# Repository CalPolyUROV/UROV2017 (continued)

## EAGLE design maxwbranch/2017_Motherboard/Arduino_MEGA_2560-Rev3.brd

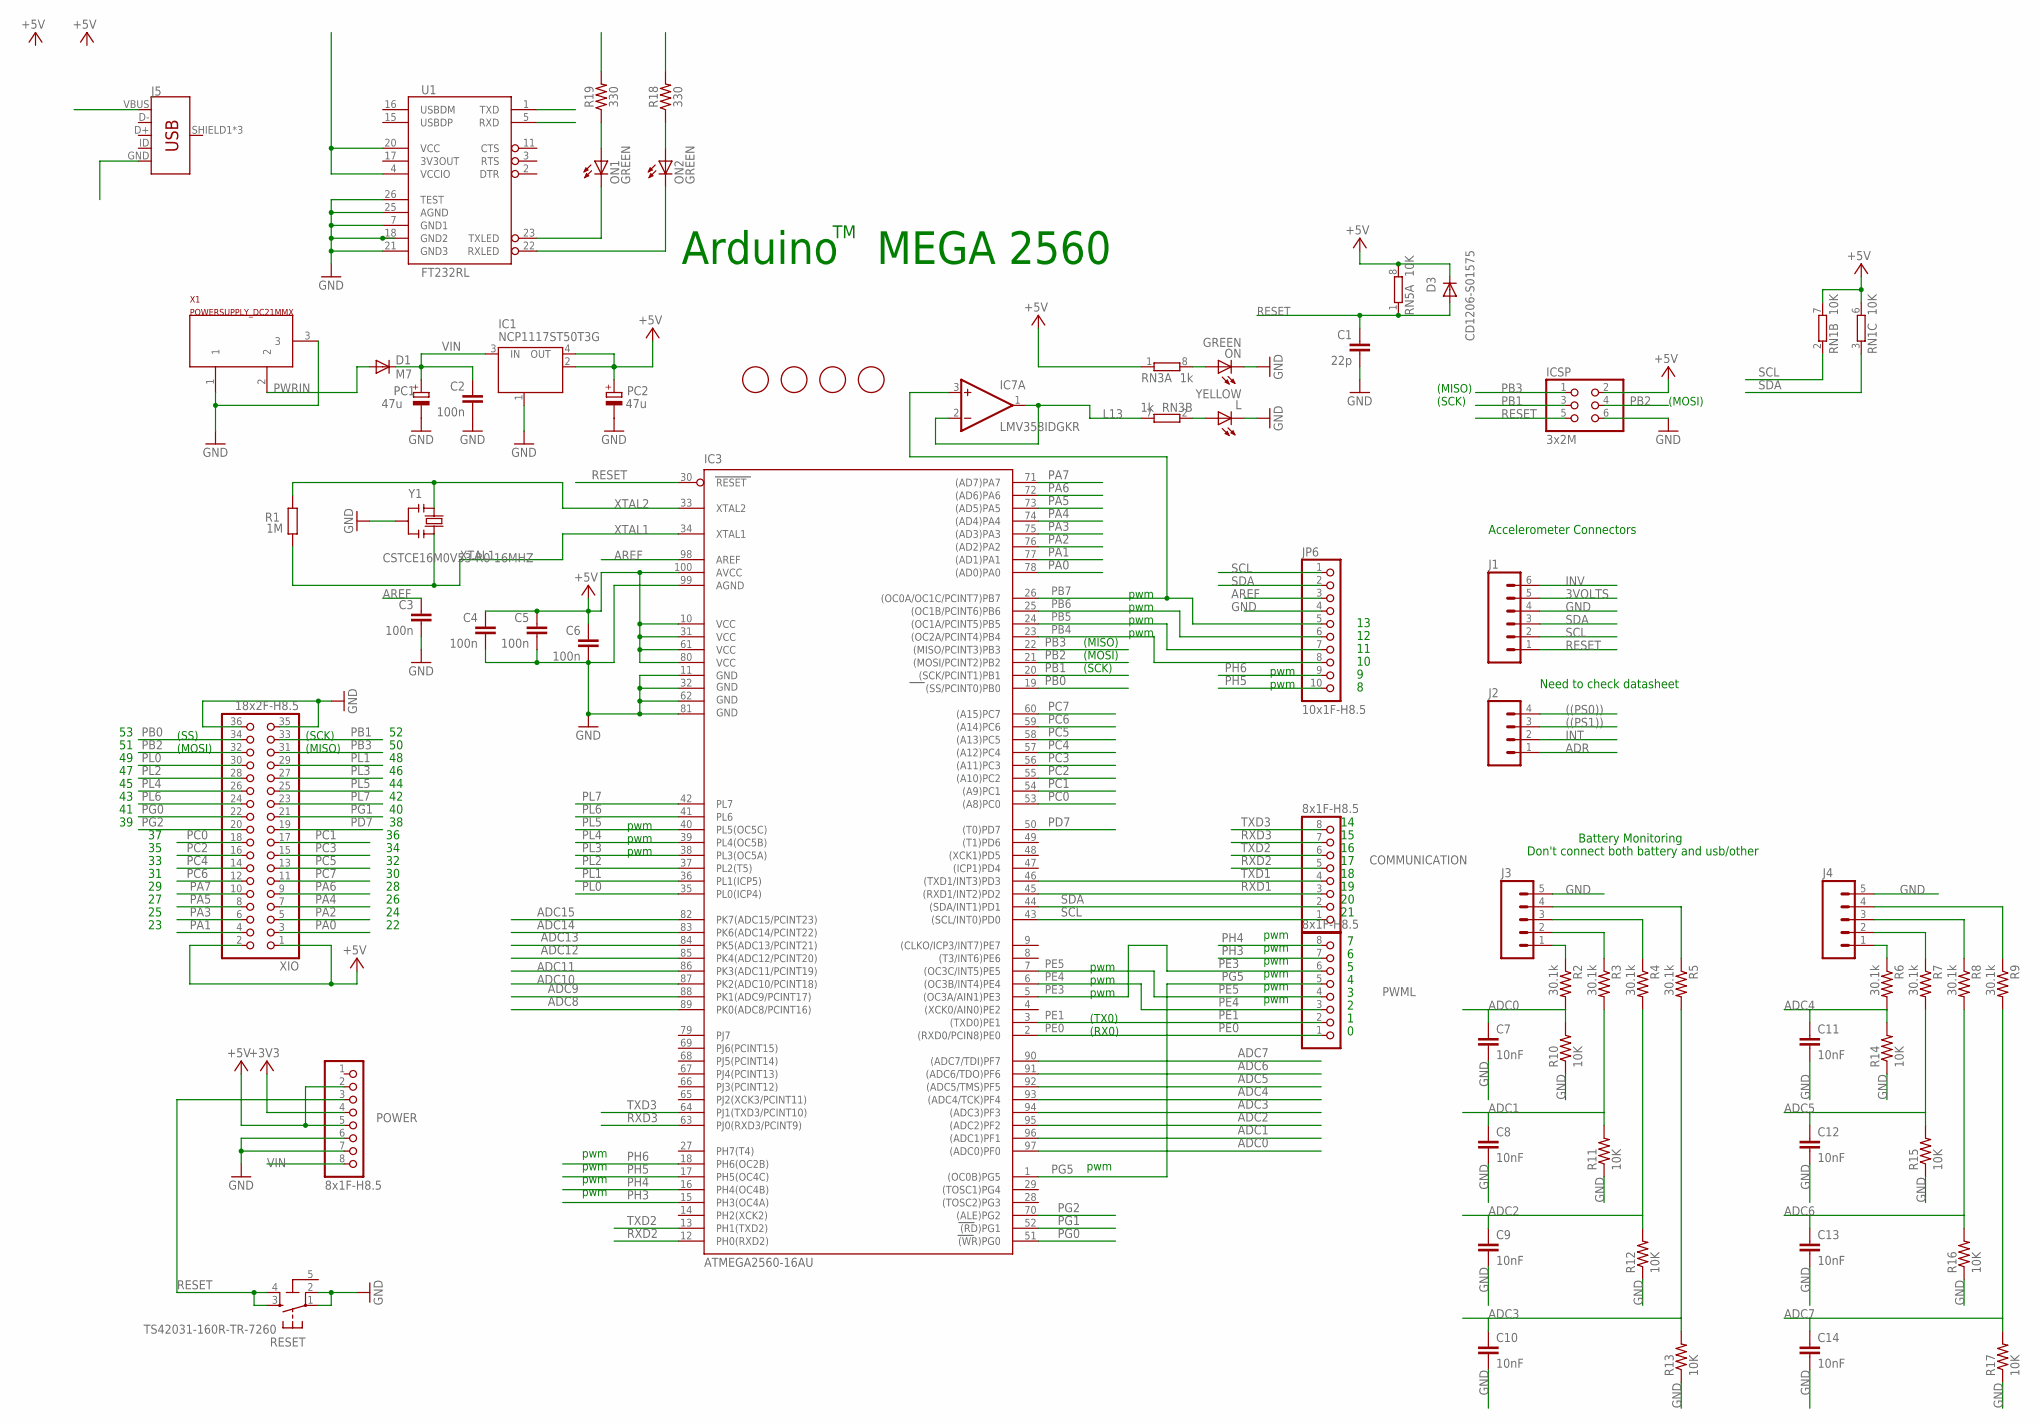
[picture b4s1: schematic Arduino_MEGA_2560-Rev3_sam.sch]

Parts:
C1: 22p; C0603-ROUND
C2, C3, C4, C5, C6: 100n; C0603-ROUND
C7, C8, C9, C10, C11, C12, C13, C14: 10nF; 0603-CAP
COMMUNICATION: 8x1F-H8.5; 1X08
D1: M7; SMB
D3: CD1206-S01575; MINIMELF
FD1, FD2, FD3, FD4: FIDUCIALMOUNT; FIDUCIA-MOUNT
IC1: NCP1117ST50T3G; SOT223
IC3: ATMEGA2560-16AU; TQFP100
IC7: LMV358IDGKR; MSOP08
ICSP: 3x2M; 2X03
J1: M06LONGPADS; 1X06_LONGPADS
J2: M04LONGPADS; 1X04_LONGPADS
J3, J4: M05JST-VERT; JST-5-PTH-VERT
J5: USB_MICRO-B_FEMALE-SMT; USB-B-MICRO-SMD
JP6: 10x1F-H8.5; 1X10
L: YELLOW; CHIP-LED0805
ON, ON1, ON2: GREEN; CHIP-LED0805
PC1, PC2: 47u; PANASONIC_D
POWER: 8x1F-H8.5; 1X08
PWML: 8x1F-H8.5; 1X08
R1: 1M; R0603-ROUND
R2, R3, R4, R5, R6, R7, R8, R9: 30.1k; 0603-RES
R10, R11, R12, R13, R14, R15, R16, R17: 10K; 0603-RES
R18, R19: 330; 0603
RESET: TS42031-160R-TR-7260; TS42
RN1, RN5: 10K; CAT16
RN3: 1k; CAY16
U1: FT232RL; SSOP28DB
X1: POWERSUPPLY_DC21MMX; POWERSUPPLY_DC-21MM
XIO: 18x2F-H8.5; 2X18
Y1: CSTCE16M0V53-R0 16MHZ; RESONATOR

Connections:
3VOLTS: J1.5
5-GND: RESET.5 (5-GND)
((PS0)): J2.4
((PS1)): J2.3
+3V3: POWER.4
+5V: C4.1, C5.1, C6.1, D3.C, IC1.2 (OUT), IC1.4 (OUT), IC3.10 (VCC), IC3.31 (VCC1), IC3.61 (VCC2), IC3.80 (VCC3), IC3.100 (AVCC), ICSP.2, PC2.+, POWER.2, POWER.5, RN1.6 (2), RN1.7 (2), RN3.1, RN5.8 (2), XIO.1, XIO.2
ADC0: C7.1, IC3.97 ((ADC0)PF0), R2.2, R10.2
ADC1: C8.1, IC3.96 ((ADC1)PF1), R3.2, R11.2
ADC2: C9.1, IC3.95 ((ADC2)PF2), R4.2, R12.2
ADC3: C10.1, IC3.94 ((ADC3)PF3), R5.2, R13.2
ADC4: C11.1, IC3.93 ((ADC4/TCK)PF4), R6.2, R14.2
ADC5: C12.1, IC3.92 ((ADC5/TMS)PF5), R7.2, R15.2
ADC6: C13.1, IC3.91 ((ADC6/TDO)PF6), R8.2, R16.2
ADC7: C14.1, IC3.90 ((ADC7/TDI)PF7), R9.2, R17.2
ADC8: IC3.89 (PK0(ADC8/PCINT16))
ADC9: IC3.88 (PK1(ADC9/PCINT17))
ADC10: IC3.87 (PK2(ADC10/PCINT18))
ADC11: IC3.86 (PK3(ADC11/PCINT19))
ADC12: IC3.85 (PK4(ADC12/PCINT20))
ADC13: IC3.84 (PK5(ADC13/PCINT21))
ADC14: IC3.83 (PK6(ADC14/PCINT22))
ADC15: IC3.82 (PK7(ADC15/PCINT23))
ADR: J2.1
AREF: C3.1, IC3.98 (AREF), JP6.3
GND: C1.2, C2.2, C3.2, C4.2, C5.2, C6.2, C7.2, C8.2, C9.2, C10.2, C11.2, C12.2, C13.2, C14.2, IC1.1 (GND/ADJ), IC3.11 (GND), IC3.32 (GND1), IC3.62 (GND2), IC3.81 (GND3), IC3.99 (AGND), ICSP.6, J1.4, J3.5, J4.5, JP6.4, L.C, ON.C, PC1.-, PC2.-, POWER.6, POWER.7, R10.1, R11.1, R12.1, R13.1, R14.1, R15.1, R16.1, R17.1, RESET.1, RESET.2, U1.7 (GND1), U1.18 (GND2), U1.21 (GND3), U1.25 (AGND), U1.26 (TEST), X1.1, X1.3, XIO.35, XIO.36, Y1.2
INT: J2.2
INV: J1.6
L13: IC7.1 (OUT), IC7.2 (-IN), RN3.7 (2)
unnamed: J3.1, R2.1
unnamed: L.A, RN3.2 (1)
unnamed: ON.A, RN3.8 (2)
unnamed: ON1.A, R19.1
unnamed: J4.1, R6.1
unnamed: J3.2, R3.1
unnamed: J3.3, R4.1
unnamed: ON2.A, R18.1
unnamed: J3.4, R5.1
unnamed: J4.2, R7.1
unnamed: J4.3, R8.1
unnamed: J4.4, R9.1
unnamed: ON1.C, U1.23 (TXLED)
unnamed: ON2.C, U1.22 (RXLED)
unnamed: U1.4 (VCCIO), U1.20 (VCC)
PA0: IC3.78 ((AD0)PA0), XIO.3
PA1: IC3.77 ((AD1)PA1), XIO.4
PA2: IC3.76 ((AD2)PA2), XIO.5
PA3: IC3.75 ((AD3)PA3), XIO.6
PA4: IC3.74 ((AD4)PA4), XIO.7
PA5: IC3.73 ((AD5)PA5), XIO.8
PA6: IC3.72 ((AD6)PA6), XIO.9
PA7: IC3.71 ((AD7)PA7), XIO.10
PB0: IC3.19 ((SS/PCINT0)PB0), XIO.34
PB1: IC3.20 ((SCK/PCINT1)PB1), ICSP.3, XIO.33
PB2: IC3.21 ((MOSI/PCINT2)PB2), ICSP.4, XIO.32
PB3: IC3.22 ((MISO/PCINT3)PB3), ICSP.1, XIO.31
PB4: IC3.23 ((OC2A/PCINT4)PB4), JP6.8
PB5: IC3.24 ((OC1A/PCINT5)PB5), JP6.7
PB6: IC3.25 ((OC1B/PCINT6)PB6), JP6.6
PB7: IC3.26 ((OC0A/OC1C/PCINT7)PB7), IC7.3 (+IN), JP6.5
PC0: IC3.53 ((A8)PC0), XIO.18
PC1: IC3.54 ((A9)PC1), XIO.17
PC2: IC3.55 ((A10)PC2), XIO.16
PC3: IC3.56 ((A11)PC3), XIO.15
PC4: IC3.57 ((A12)PC4), XIO.14
PC5: IC3.58 ((A13)PC5), XIO.13
PC6: IC3.59 ((A14)PC6), XIO.12
PC7: IC3.60 ((A15)PC7), XIO.11
PD7: IC3.50 ((T0)PD7), XIO.19
PE0: IC3.2 ((RXD0/PCIN8)PE0), PWML.1
PE1: IC3.3 ((TXD0)PE1), PWML.2
PE3: IC3.5 ((OC3A/AIN1)PE3), PWML.6
PE4: IC3.6 ((OC3B/INT4)PE4), PWML.3
PE5: IC3.7 ((OC3C/INT5)PE5), PWML.4
PG0: IC3.51 ((WR)PG0), XIO.22
PG1: IC3.52 ((RD)PG1), XIO.21
PG2: IC3.70 ((ALE)PG2), XIO.20
PG5: IC3.1 ((OC0B)PG5), PWML.5
PH3: IC3.15 (PH3(OC4A)), PWML.7
PH4: IC3.16 (PH4(OC4B)), PWML.8
PH5: IC3.17 (PH5(OC4C)), JP6.10
PH6: IC3.18 (PH6(OC2B)), JP6.9
PL0: IC3.35 (PL0(ICP4)), XIO.30
PL1: IC3.36 (PL1(ICP5)), XIO.29
PL2: IC3.37 (PL2(T5)), XIO.28
PL3: IC3.38 (PL3(OC5A)), XIO.27
PL4: IC3.39 (PL4(OC5B)), XIO.26
PL5: IC3.40 (PL5(OC5C)), XIO.25
PL6: IC3.41 (PL6), XIO.24
PL7: IC3.42 (PL7), XIO.23
PWRIN: D1.A, X1.2
RESET: C1.1, D3.A, IC3.30 (RESET), ICSP.5, J1.1, POWER.3, RESET.3, RESET.4, RN5.1
RXD: U1.1 (TXD)
RXD1: COMMUNICATION.3, IC3.45 ((RXD1/INT2)PD2)
RXD2: COMMUNICATION.5, IC3.12 (PH0(RXD2))
RXD3: COMMUNICATION.7, IC3.63 (PJ0(RXD3/PCINT9))
SCL: COMMUNICATION.1, IC3.43 ((SCL/INT0)PD0), J1.2, JP6.1, RN1.2 (1)
SDA: COMMUNICATION.2, IC3.44 ((SDA/INT1)PD1), J1.3, JP6.2, RN1.3 (1)
TXD1: COMMUNICATION.4, IC3.46 ((TXD1/INT3)PD3)
TXD2: COMMUNICATION.6, IC3.13 (PH1(TXD2))
TXD3: COMMUNICATION.8, IC3.64 (PJ1(TXD3/PCINT10))
V+: IC7.8 (V+)
V-: IC7.4 (V-)
VIN: C2.1, D1.C, IC1.3 (IN), PC1.+, POWER.8
XTAL1: IC3.34 (XTAL1), R1.1, Y1.3
XTAL2: IC3.33 (XTAL2), R1.2, Y1.1

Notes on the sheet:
Arduino MEGA 2560
(SCK)
(MISO)
(MOSI)
pwm
(TX0)
(RX0)
(SS)
Accelerometer Connectors
Battery Monitoring
Need to check datasheet
Don't connect both battery and usb/other

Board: 2 copper layers, 66 parts (0 on the bottom side), 86 nets, no tracks yet.

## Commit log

2016-10-29 started repo with a readme
2016-10-29 Added info
2016-10-29 Added Main UI
2016-10-29 Tutorial
2016-10-29 nothing serious
2016-10-29 Organizing the Github directories
2016-10-29 Moved Pygame funcs and Objs to raper class
    Functions and objects from pygame were moved to UIUtils.py file to make
    things more simplyfied and more objected oriented
2016-10-29 More directory organization
2016-10-29 Added Accelerometer Code
    Three - axis data retrieval for Arduino.
2016-10-29 Changed Controller to be object oriented
    Changed Controller to be object oriented and made code simpler and more
    organized
2016-10-29 Merging LMPS into Master
2016-11-01 Add To-Do List
    Transcribed from picture of whiteboard provided by Kyle
2016-11-05 Create Folder and readme for accel
2016-11-05 Add data sheets to readme
2016-11-05 Add Adafruit library
2016-11-05 Added shouldQuit func and fixed minor bugs
    Added shouldQuit func and fixed minor bugs related with data filtering
    and reading funcs
2016-11-05 Add sample orientation code
2016-11-05 Remove library that shouldnt be kept here
2016-11-05 Added current version of firmware starter files
2016-11-05 Added folders
2016-11-05 Add callibration sample code
2016-11-12 Commnet code
2016-11-12 Add linear accelerometer data
2016-11-12 Add adafruit data sheet
2016-11-12 Clean up commented code
2016-11-12 Added DataHandling.py and ArtificialHorizon.py
    Added DataHandling.py and ArtificialHorizon.py to make the UI more
    efficient and object oriented
2016-12-03 Add time keeping
2016-12-03 Add Serial_print function
2016-12-03 Handle all the data as arrays
2016-12-03 Calculate velocity and Position from acceleration
2016-12-03 Document current configuration of wires
2016-12-03 Use floats instead of ints in arrays
2016-12-03 convert elapsed time factor to float
    unsigned long lacks decimal
2016-12-03 reduce startup delay
2016-12-03 convert serial_print to float
2016-12-03 reduce number of decimal points printed
    fixes jittery console
2016-12-03 commnet out orientation
2016-12-03 remove odl printing code
2016-12-03 Fix elapsed time factor
    at printing test
2016-12-03 print velocity and position
2016-12-03 reminder about bugs
2016-12-03 Added Doc
    Added Doc for files: ArtificialHorizion.py, controller.py,
    DataHandling.py, serial_finder.py and UIUtils.py
2016-12-03 use better time tracking
2016-12-03 add filter helper function
2016-12-03 filter acceleration
2016-12-03 comment out printing of position
    still doing calculations
2016-12-03 work on drift
2016-12-03 Initial commit, reads temp data from DS18B20 sensor
2016-12-03 Added MotHandling
    Added MotHandling so it has bars representing the data that change color
    with value.
2016-12-03 Added first version of autopilot
    added first version of autopilot
2016-12-03 make filter value configurable
2016-12-03 Only print based on an index
    every 20 polls
2016-12-03 begin work on changing coord system
2017-01-14 Motherboard
    added motherboard to github
2017-01-14 add whiteboard translation notes
2017-01-14 changed to 10-bit resolution, 200 ms per conversion
2017-01-14 Add Lookup values generator
    Added an arduino program for generating values to be coded into a lookup
    table
2017-01-14 Create TrigLookup Library
2017-01-14 Revert "Create TrigLookup Library"
    This reverts commit c69d96d2355d265a32383e8425ed06a8d6e10551.
2017-01-14 Make event allocated earlier
2017-01-14 Use pitch, roll, and yaw instead of array
2017-01-14 typo
2017-01-14 Remove filter
    not effective
2017-01-14 Change/remove delays
2017-01-14 Add lookup table for Sin and Cos
2017-01-14 Use trig translation and lokoup table for accel
2017-01-14 changes to loop indexing
2017-01-14 Put sin_list back as a global variable
    it uses so much memory D:
2017-01-14 set print to not make a mess
2017-01-21 Split code into functions
2017-01-21 Added stock github files of the accelerometer
2017-01-21 Added test file
2017-01-21 Make orientation ints
2017-01-21 Reverse pitch and yaw
2017-01-21 Add threshold and print functions
2017-01-21 comment out acceleration translation
2017-01-21 FTDI FT232RL
    Created schematic module for FTDI FT232RL. Version 1
2017-01-21 FT232RL Schematic
    Version 1
2017-01-21 Notes on spark fun accelerometer
2017-01-21 FTDI_Module Folder
2017-01-21 FTDI/FT232RL
    Added another pull-down to CBUS1
2017-01-21 Create library source
2017-01-21 Create Library header
2017-01-21 Migrate library functions out of main file
2017-01-21 Beginning to clean up master code
    Starting to remove what we don't need, and make room for what we do.
    Summary of changes to be made in README.txt
2017-01-23 Motherboard accelerometer + FTDI
    updated to current FTDI and accelerometer on the schematic
2017-01-23 Added GND for PWMs
2017-01-23 Added ESC hex file
2017-01-28 Moving the graveyard, code compiles now
2017-01-28 SchematicRev1
    finished the schematic (hopefully), now we will work on the layout
2017-01-28 Rename and finish library files
2017-01-28 Now it compiles
2017-01-28 switched led on USB line to parallel
    LED will now not drop the voltage
2017-01-29 remove old commented out code
2017-01-29 change orders
2017-02-02 Continuing to fix up main code
2017-02-04 Added RS485 and video switching
    Added several new parts to schematic. Hopefully the library transfers
    with it. If not, download the maxim parts library for eagle
2017-02-04 Updated part names
    minor changes
2017-02-04 Sat feb 4
2017-02-04 Getting closer to working
2017-02-05 Finalized schematic and began layout
    FTDI chip is complete, although the AGND on it is a floating pin at the
    moment. The RESET_B was changed to RESET on the schematic
2017-02-11 Final state as a library
2017-02-11 Revert to minized main code
2017-02-16 Video Out Laid out
2017-02-17 Revert "Video Out Laid out", schematic lost video
    This reverts commit bce98d3cfb039a053e1cc747be892bf7f1308c0a.
2017-02-18 Reverted schematic and Layout
    took out video and and added support for orientation sensor. schematic
    and layout are in sync again
2017-02-20 Power board changes
2017-02-20 Motherboard routing
2017-02-21 More motherboard tinkering
2017-02-21 Power Supply Board changes
2017-02-21 Power board updates
2017-02-21 Power Supply Labeling
2017-02-25 Revert "Revert to minized main code"
    This reverts commit 11f3631f3ad15e9da63149d103f8170585e335aa.
2017-02-25 add minimized accelerometer
2017-02-25 Add accelerometer to main arduino
2017-02-25 removed commneted out code
2017-02-25 Add BNO055 libraries
2017-02-25 Routed power
    Working on AREF plane
2017-02-25 Code with BNO055 now compiles
    Successfully uses a downloaded BNO055 library, so library code doesn't
    have to be put in the main directory
2017-03-02 Minor fixes
2017-03-04 Testing main code on Sebastian's brains
2017-03-04 Half of routing done
    fixed errors in ERC, removed op amp on pin 13, disconnected AREF and
    changed to AGND. AGND separated from GND by 1M resistor. Video routing
    TBD. AGND plane TBD?
2017-03-05 slight routing additions
2017-03-11 Power gerber generated
2017-03-11 Added more routing for video
    video routing
2017-03-11 Ported to Raspberry Pi and added Camera
    Modified the UI to be compatible with raspberry pis and added camera
    support
2017-03-11 Finished routing
    routing is done, need to remove the three duplicate pins
2017-03-20 final changes for FAB
2017-04-15 Additional changes
2017-05-06 Pins used are in README file
2017-05-06 First functional function of the 3.0 UI
    First functional function of the 3.0 UI tested with the bot. Some bugs
    need to be solved
2017-05-08 Bug Fixes
    Bug Fixes
2017-05-08 Fixing up main, adding secondary Arduino for steppers
2017-05-08 Added Doc
    Added Documentation about the communication had shake.
2017-05-19 Code as of 5/13
2017-06-03 remove comment
2017-06-10 Adding Bluetooth
2017-09-16 Adapted for Sebastian
    Fixed bugs, added debug messages and adapted the UI for sebastian
2017-09-30 set serial3 baudrate to 115200 to match UI
2017-10-07 Added debug prints
    Added debug prints
2017-10-14 add new Eagle project for 2018
2017-10-14 eaga
2017-10-14 add pinout spreadsheet
2017-10-15 new eagle schematic
2017-10-15 add old schematic pdf
2017-10-15 add pin map reference image
2017-10-15 complete pin map spreadsheet
